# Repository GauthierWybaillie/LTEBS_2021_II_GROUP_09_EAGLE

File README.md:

# LTEBS_2021_II_GROUP_09_EAGLE

21.03.21
  1.TMUX has been modified because there was an error in the schematic found on beep, the official datasheet from texas instruments https://www.ti.com/lit/ds/symlink/tmux1208.pdf?ts=1615825592091 layout has been assumed.
  2.assignment1_LBR.lbr shows some discordances in the layers usage (tname layer should be used for names as well as tvalue for values), the symbol has been centered.
(there is some confusion in the log on march 21, I uploaded the version directly on main, wrongly. Everything should be ok now)
                                                            Oswaldo.

23.03.21
  1. Board.brd revised. Components have been moved in order to save pcb space. Dimensions and spk.scr added to be more conform with the class about Eagle.

26.03.21
  1.Final version created

# LTEBS_2021_II_GROUP_09_EAGLE

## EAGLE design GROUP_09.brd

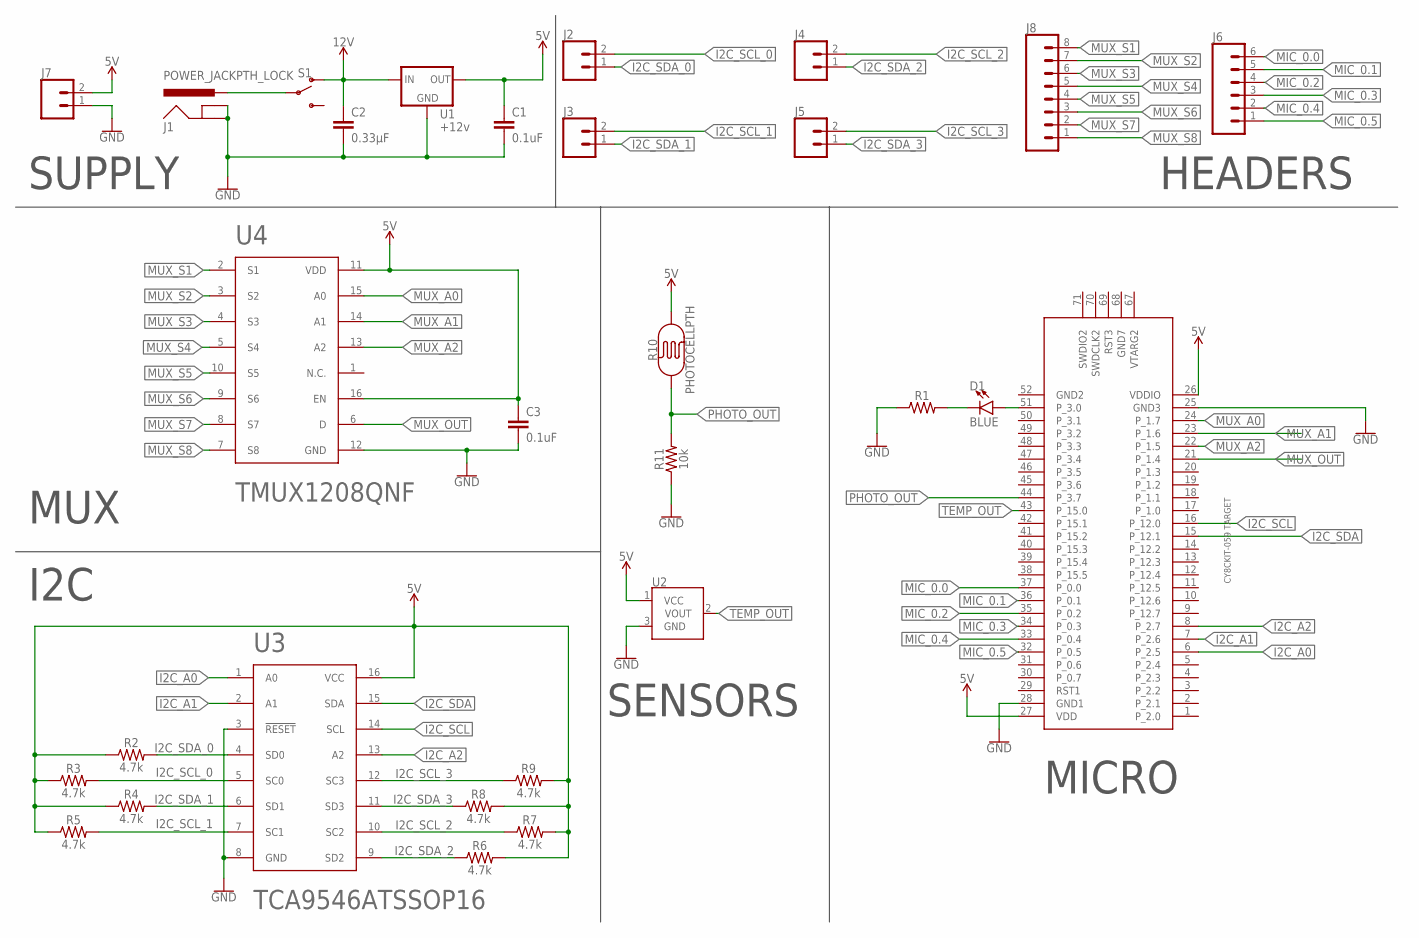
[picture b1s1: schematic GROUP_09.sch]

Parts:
C1, C3: 0.1uF; CAP-PTH-SMALL-KIT
C2: 0.33µF; 0805
CY8CKIT059-TARGET: CY8CKIT-059_TARGET
D1: BLUE; LED-1206
J1: POWER_JACKPTH_LOCK; POWER_JACK_PTH_LOCK
J2, J3, J4, J5, J7: 1X02
J6: 1X06_LOCK
J8: 1X08_LOCK
R1: AXIAL-0.3
R2, R3, R4, R5, R6, R7, R8, R9: 4.7k; 0603
R10: PHOTOCELLPTH; PHOTOCELL
R11: 10k; 0603
S1: SWITCH_SPDT_PTH_11.6X4.0MM
U1: +12v; TO-252
U2: TO-92
U3: TCA9546ATSSOP16; TSSOP-16
U4: TMUX1208QNF; QFN-16

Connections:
5V: C1.1, C3.1, CY8CKIT059-TARGET.26 (VDDIO), CY8CKIT059-TARGET.27 (VDD), J7.2, R2.1, R3.1, R4.1, R5.1, R6.2, R7.2, R8.2, R9.2, R10.2, U1.2 (OUT), U2.1 (VCC), U3.16 (VCC), U4.11 (VDD), U4.16 (EN)
12V: C2.1, S1.1 (O), U1.1 (IN)
GND: C1.2, C2.2, C3.2, CY8CKIT059-TARGET.25 (GND3), CY8CKIT059-TARGET.28 (GND1), J1.GND, J1.GNDBREAK, J7.1, R1.P$1 (1), R11.1, U1.3 (GND), U2.3 (GND), U3.3 (!RESET!), U3.8 (GND), U4.12 (GND)
I2C_A0: CY8CKIT059-TARGET.6 (P_2.5), U3.1 (A0)
I2C_A1: CY8CKIT059-TARGET.7 (P_2.6), U3.2 (A1)
I2C_A2: CY8CKIT059-TARGET.8 (P_2.7), U3.13 (A2)
I2C_SCL: CY8CKIT059-TARGET.16 (P_12.0), U3.14 (SCL)
I2C_SCL_0: J2.2, R3.2, U3.5 (SC0)
I2C_SCL_1: J3.2, R5.2, U3.7 (SC1)
I2C_SCL_2: J4.2, R7.1, U3.10 (SC2)
I2C_SCL_3: J5.2, R9.1, U3.12 (SC3)
I2C_SDA: CY8CKIT059-TARGET.15 (P_12.1), U3.15 (SDA)
I2C_SDA_0: J2.1, R2.2, U3.4 (SD0)
I2C_SDA_1: J3.1, R4.2, U3.6 (SD1)
I2C_SDA_2: J4.1, R6.1, U3.9 (SD2)
I2C_SDA_3: J5.1, R8.1, U3.11 (SD3)
MIC_0.0: CY8CKIT059-TARGET.37 (P_0.0), J6.6
MIC_0.1: CY8CKIT059-TARGET.36 (P_0.1), J6.5
MIC_0.2: CY8CKIT059-TARGET.35 (P_0.2), J6.4
MIC_0.3: CY8CKIT059-TARGET.34 (P_0.3), J6.3
MIC_0.4: CY8CKIT059-TARGET.33 (P_0.4), J6.2
MIC_0.5: CY8CKIT059-TARGET.32 (P_0.5), J6.1
MUX_A0: CY8CKIT059-TARGET.24 (P_1.7), U4.15 (A0)
MUX_A1: CY8CKIT059-TARGET.23 (P_1.6), U4.14 (A1)
MUX_A2: CY8CKIT059-TARGET.22 (P_1.5), U4.13 (A2)
MUX_OUT: CY8CKIT059-TARGET.21 (P_1.4), U4.6 (D)
MUX_S1: J8.8, U4.2 (S1)
MUX_S2: J8.7, U4.3 (S2)
MUX_S3: J8.6, U4.4 (S3)
MUX_S4: J8.5, U4.5 (S4)
MUX_S5: J8.4, U4.10 (S5)
MUX_S6: J8.3, U4.9 (S6)
MUX_S7: J8.2, U4.8 (S7)
MUX_S8: J8.1, U4.7 (S8)
unnamed: J1.PWR, S1.2
unnamed: CY8CKIT059-TARGET.51 (P_3.0), D1.A
unnamed: D1.C, R1.P$2 (2)
PHOTO_OUT: CY8CKIT059-TARGET.44 (P_3.7), R10.1, R11.2
TEMP_OUT: CY8CKIT059-TARGET.43 (P_15.0), U2.2 (VOUT)

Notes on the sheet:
MUX
I2C
HEADERS
SUPPLY
SENSORS
MICRO

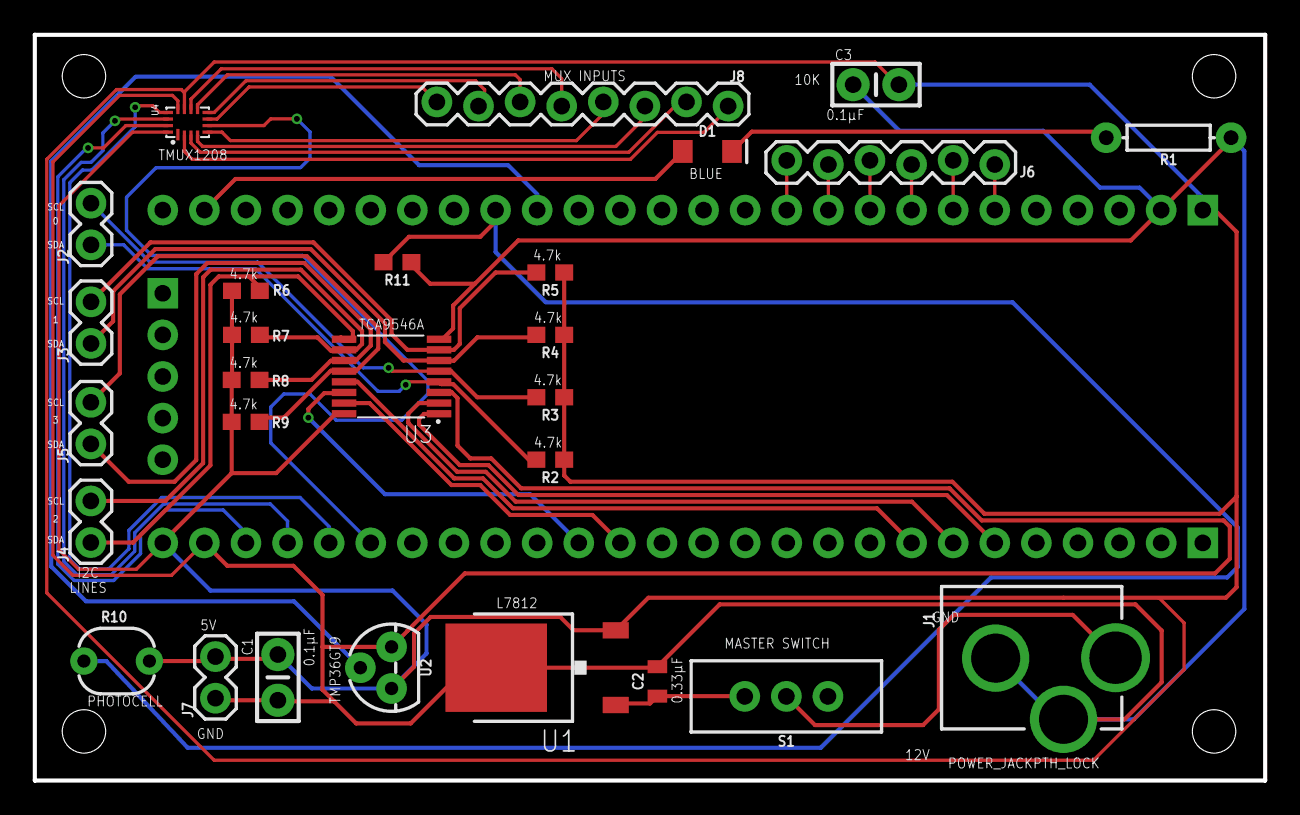
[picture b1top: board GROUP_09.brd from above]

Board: 2 copper layers, 75.1 x 45.5 mm, 29 parts (1 on the bottom side), 39 nets.

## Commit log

2021-03-20 test board upload
2021-03-20 TMUX library
2021-03-21 library TCA9546A
2021-03-21 modifications explained in README under 21.03.21
2021-03-21 uploaded now in Oswaldo branch
2021-03-21 moved to oswaldo branch
2021-03-21 updated on 21.03.21
2021-03-22 schematic V1.00
2021-03-22 board V1.00
2021-03-22 board V1.01
2021-03-22 Merged library with both components
2021-03-22 Board V1.02
2021-03-22 Schematic V1.02
2021-03-23 Adjustment board smaller, dimensions, grid
2021-03-26 .gitignore
2021-03-26 Final version

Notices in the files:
parts and their libraries:
SparkFun-Capacitors: Licensing: Creative Commons ShareAlike 4.0 International - https://creativecommons.org/licenses/by-sa/4.0
